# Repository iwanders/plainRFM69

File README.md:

plainRFM69
=========

This is a library for HopeRF's RFM69 radio series. The main goal of this library
is to use the hardware as efficiently as possible. With this goal in mind, the
used approach is different from that of the already existing libraries for this
radio module.

Approach
-------
The library is composed of two parts, the first; bareRFM69 provides a bare bones
interface to the hardware. It does nothing by itself and only provides methods
to interact with the hardware. Most of the configuration parameters are listed
in the header file. Constants are used for easy configuration and to prevent
having to look up parameters in the datasheet.
It uses the the new SPI transaction system.

The second part; plainRFM69, provides the user with more relevant functions for
sending messages. It allows for easy sending and receiving of packets. It
contains an internal buffer for received messages. Both receiving and
transmitting packets is done using the RFM69's AutoMode system. Which means the
radio spends as little time as possible in the transmitter phase and that
received packets can be retrieved from the module efficiently. This also allows
the send methods to be non-blocking, as it is unnecessary to wait until the
radio completes transmission.

Internal Workings
---------------
The plainRFM69 class provides several methods to configure the radio module with
its recommended parameters. The module is used in packet mode. Variable length
and address filtering is supported. 

The AutoMode system (described on page 42 of the RFM69CW datasheet) allows the
radio to change its mode based on a start condition, it then enters the
Intermediate Mode until an exit condition is met. 

### Receiving
By default, the radio is listening for packets. The AutoMode is configured such
that the radio goes to standby when a packet is received. This means that the
radio waits until that packet is retrieved by the microcontroller before it
starts listening for packets again. Retrieval of this packet is done with the
poll() method, which writes the packet to the internal buffer of plainRFM69.
Once the packet had been read, the radio automatically returns to listening to
packets.

### Sending
When a packet is to be transmitted, the radio is placed into standby mode. The
AutoMode is configured such that the radio automatically switches to transmitter
mode when there are bytes in the FIFO. It leaves transmission mode after the
packet is completely sent. This ensures that the transmitter is enabled 
exactly for the time necessary to sent the packet. The next time poll() is
called, the radio is configured for receiving packets with the AutoMode, as 
described in the previous paragraph.

### Interrupt
If the radio has received a packet, it waits in the Intermediate Mode until the
packet is read from the FIFO. When a packet is transmitted, the radio is in the
Intermediate Mode until the packet is completely sent. The radio module can
represent whether it is in the Intermediate State on a digital IO pin (DIO2).
In a slightly different way the same can be achieved using the DIO0 pin from the
radio module, see the `PingPongHPdio0` example on how to use that pin.

The microcontroller can attach an interrupt to this pin and call the poll()
method on every change. This means that if a packet is received, the
intermediate state is entered, DIO2 will switch from LOW to HIGH, resulting in
an interrupt trigger on the microcontroller, this calls poll() which reads the
packet from the FIFO, after this the radio automatically returns to receiving
state. The same method is possible with transmissions, where the poll() switches
the radio back to receiver mode after the transmission is complete. This means
that the microcontroller does not have to wait until the transmission is
complete, as this is also managed by the same interrupt and subsequent poll()
call. So the method to send a packet does not block until the transmission is
complete.

Testing & Performance
-------------------
The library was developed and tested on two [Teensy 3.1][teensy31]'s with
RFM69CW's attached. The pins used are described in the examples. The library is
tested with Arduino 1.0.6, 1.8.5. The DIO0 example was developed using
AdaFruit Feather M0 with the RFM69HCW radio module. Arduino and Moteino are also
known to work.

All tests were performed with the radio modules located next to each other. The
measured results are of course dependent on the parameters chosen, the
values from the examples show below use a GFSK modulation at 300000 bps.

#### Maximum_Speed
Sends 64 byte packets from the sender to the receiver. For every message sent
a counter is incremented. This counter is repeated in the message to create the
payload. At the receiver the payload is checked and the counter is used to check
whether there were missed packets.
```
Total packets: 101600
Packetloss count: 1
Per second: 416
```
This example can also be used to verify that the internal buffer is working. For
example when a delay is introduced in the loop of the receiver.

#### Maximum_PingPong
Sends 64 byte packets from the sender to the receiver, which echoes the packet,
the sender waits for this echo and checks the counter and message payload.
```
Successful pingpongs: 123468
Incorrect pingpongs: 0
Timeout pingpongs: 0
Successful / second: 188
Average ping (uSec): 5313
```

#### Buffering
The internal buffer of bareRFM69 is demonstrated in the BusyMan example. In this
example the interrupt mechanism is used and the receiving end is very busy in
the loop, this results in several messages queueing up in the internal buffer.
```
We are busy, doing important things!
Oh look, there are packets!
Packet (4): 2035
Packet (4): 2036
Packet (4): 2037
Packet (4): 2038
Packet (4): 2039
Packet (4): 2040
We had 6 packets in the buffer.
```

Usage
-----
As said, this library was created to be efficient. The goal was not really to be
user friendly. The examples were tested and are working without any known bugs.
Feel free to use it, but if it breaks you get to keep both parts, if you have a
fix for the problem feel free to share it.

The examples should provide pointers on how to use this, I suggest looking at
Minimal and MinimalInterrupt, where the latter should be the most minimal
implementation to build on. The internal buffering is shown in the BusyMan
example.

The header files for both bareRFM69 and plainRFM69 provide explanation of the
methods. If using a high power module, be sure to call `setHighPowerModule()` to
enable the high power functionality to be used.

Other libraries that might interest you are [Radiohead][radiohead] or
LowPowerLabs' [RFM69][rfm69] which have seen extensive testing.

The PCB's I designed to connect the radio modules to the Teensy can be found in
[extras/hardware/](extras/hardware/).

License
------
MIT License, see LICENSE.md.

Copyright (c) 2014 Ivor Wanders

[teensy31]: http://www.pjrc.com/teensy/
[radiohead]: http://www.airspayce.com/mikem/arduino/RadioHead/
[rfm69]: https://github.com/LowPowerLab/RFM69

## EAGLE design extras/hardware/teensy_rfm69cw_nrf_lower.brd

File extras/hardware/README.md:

Teensy_RFM69CW breakout
====================

This are the breakout boards I use to connect the radio module to the Teensy chips. I used two PCB's instead of one to save cost and to allow access to the pins below the radio module. Although only DIO2 is required for the library, all DIO pins are made accessible. The silkscreen on the boards is not all that clear, so I suggest opening the schematic and board files when soldering to check where the parts should go. I have switched to KiCad since making this, so I'm not going to invest any time in updating the boards.

The lower part has a jumper to connect the clock of the SPI port to either pin 13 or 14, it is connected to pin 14 by default so that the led is still available for use. This lower part also contains an 8 pin header for SPI, in the same pin-layout as the NRF24L0+ radio modules.

The upper part has a loading circuit for a LiPo battery, based on the [MAX1555][max1555] battery charger IC. It connects the Vusb from the Teensy to the USB input of the Max1555 chip, a header is provided for the DC pin of the Max1555 chip. The battery's positive lead is connected to the battery pin of the Max1555 IC and the Vin of the Teensy. Cutting the Vusb-Vin pad on the Teensy is required when using this board.

One wire is required from the upper to the lower board, this is the MISO line of the SPI port. I used a thick piece of wire for this in order to relieve the stress on the radio module when detaching the assembly from a Teensy. In case the board should also work without a battery attached, I recommend adding a larger electrolytic capacitor over the battery pins (something like 220uF should do).

Pinout for lower board
-------------

Related to the RFM69CW radio module:

| RFM           | Teensy |
| ------------- | ----------- |
| MOSI          |   11 DOUT |
| SCK           |   14 SCK2 (jumper to 13) |
| NSS           |   10 CS |
| DIO3          |   16 |

For the NRF header:

| NRF   |   Teensy |
| ------|--------- |
| CE    |   9 |
| SCK   |  14 SCK2 (jumper to 13) |
| MISO  |  12 DIN |
| CSN   |  15 CS |
| MOSI  |  11 DOUT |
| IRQ   |  Solderpad |

Pinout for the upper board
-------------------

Related to the RFM69CW radio module:

| RFM           | Teensy |
| ------------- | ----------- |
| MISO          |  Solderpad |
| RESET         |  23 |
| DIO0          |  2 |
| DIO1          |  1 |
| DIO2          |  0 |
| DIO5          | Solderpad |

Related to the charging Circuit:

| MAX1555       | Connected to          |
| ------------- | ----------- |
| Bat           | Battery header positive, Teensy Vin |
| DC            | DC input header positive |
| USB           | Teensy Vusb |
| CHG           | To an led |

Credits
---------
I used the Eagle part libraries from [Mikes-Eagle-Libraries](https://github.com/mgrusin/Mikes-Eagle-Libraries) and [SparkFun-PowerIC](https://github.com/sparkfun/SparkFun-Eagle-Libraries/blob/master/SparkFun-PowerIC.lbr). Inspiration to include the charging circuit came from [Onehorse's appallingly small LiPo Charger addon](https://forum.pjrc.com/threads/26462-Appallingly-small-LiPo-charger-add-on-for-Teensy-3-1).

Assembled
--------

[max1555]: https://www.maximintegrated.com/en/products/power/battery-management/MAX1555.html

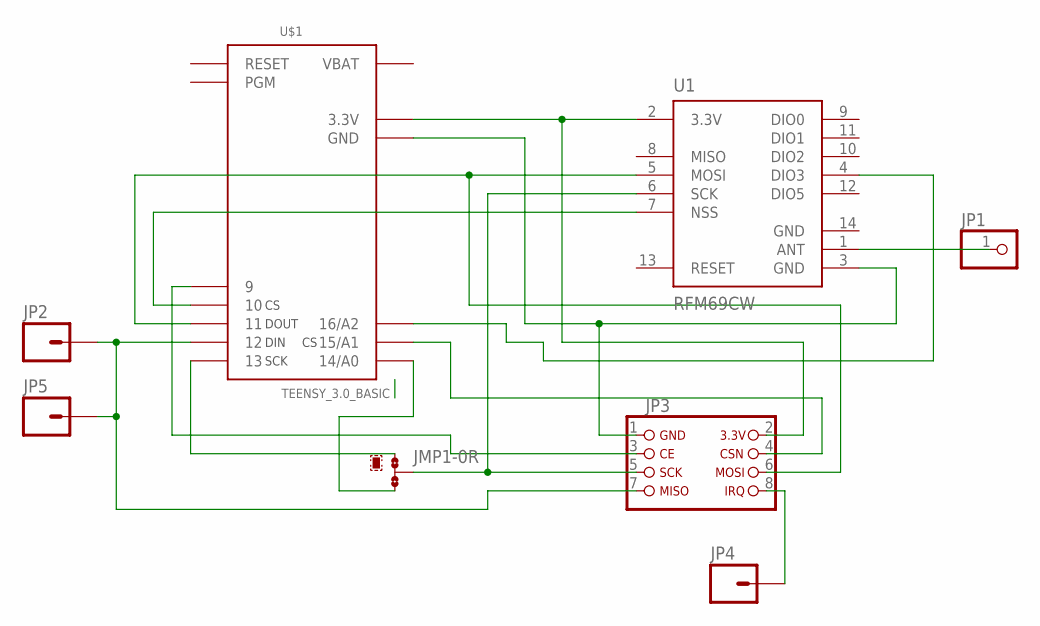
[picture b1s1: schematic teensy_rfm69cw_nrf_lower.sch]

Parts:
JMP1: 0R-JUMPA; A0R-JMP
JP1: PINHD-1X1; 1X01
JP2, JP4, JP5: M01SMD-4.5X1.5; PAD-1.5X4.5
JP3: NRF24
U1: RFM69CW; RFM69CW-XXXS2
U$1: TEENSY_3.0_BASIC

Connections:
GND: U1.14 (GND)
unnamed: JP3.2, U1.2 (3.3V), U$1.3.3V1 (3.3V)
unnamed: JP3.1, U1.3 (GND), U$1.GND1 (GND)
unnamed: JP3.4, U$1.15/A1
unnamed: JP3.6, U1.5 (MOSI), U$1.11
unnamed: JMP1.1, U$1.13
unnamed: JMP1.3, U$1.14/A0
unnamed: U1.7 (NSS), U$1.10
unnamed: U1.4 (DIO3), U$1.16/A2
unnamed: JP1.1, U1.1 (ANT)
unnamed: JMP1.2, JP3.5, U1.6 (SCK)
unnamed: JP2.P$1, JP3.7, JP5.P$1, U$1.12
unnamed: JP3.3, U$1.9
unnamed: JP3.8, JP4.P$1
VBAT: U$1.VBAT

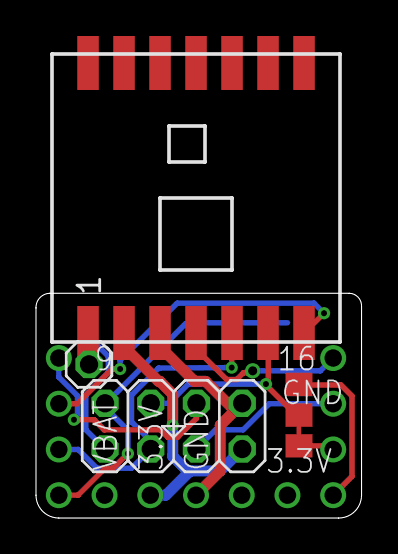
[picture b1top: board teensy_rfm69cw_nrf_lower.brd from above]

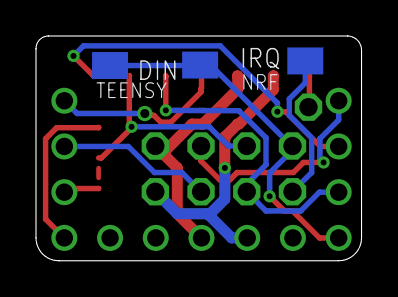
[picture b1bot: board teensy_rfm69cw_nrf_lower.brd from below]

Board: 2 copper layers, 18.1 x 12.5 mm, 8 parts (3 on the bottom side), 13 nets.

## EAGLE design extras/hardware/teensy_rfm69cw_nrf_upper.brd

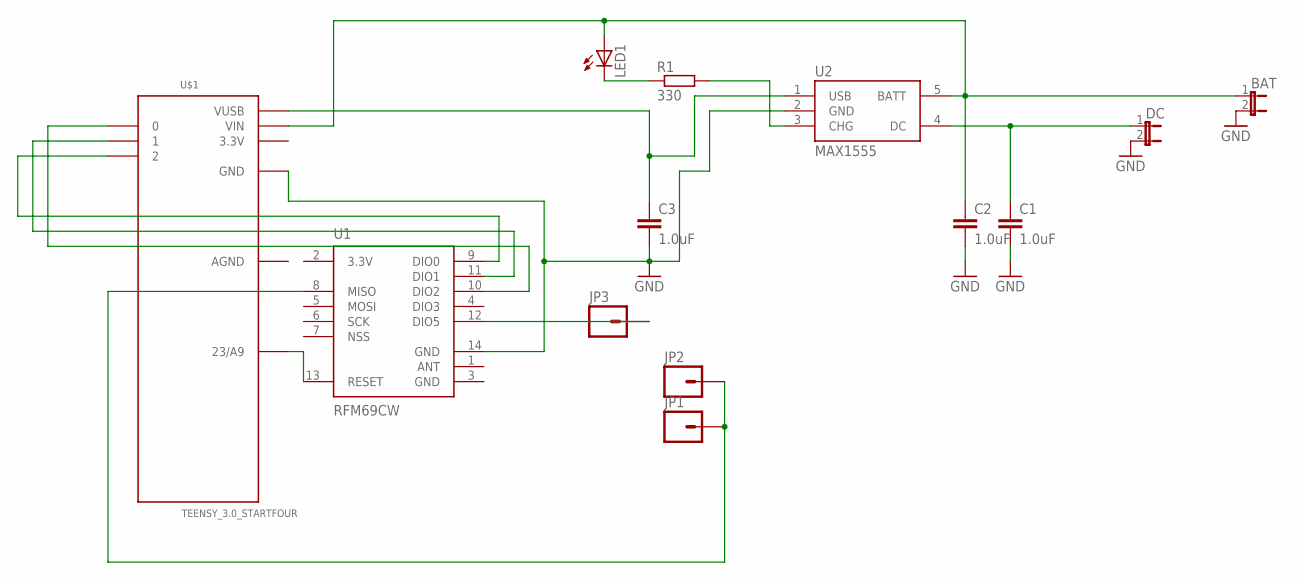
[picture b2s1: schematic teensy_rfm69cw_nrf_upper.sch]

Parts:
BAT: JP1E; JP1
C1, C2, C3: 1.0uF; 0603-CAP
DC: JP1E; JP1
JP1, JP2, JP3: M01SMD-4.5X1.5; PAD-1.5X4.5
LED1: LEDSML0603; SML0603
R1: 330; R0603
U1: RFM69CW; RFM69CW-XXXS2
U2: MAX1555; SOT23-5
U$1: TEENSY_3.0_STARTFOUR

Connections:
3.3V: U1.2 (3.3V), U$1.3.3V
AGND: U$1.AGND
GND: BAT.2, C1.2, C2.2, C3.2, DC.2, U1.3 (GND), U1.14 (GND), U2.2 (GND), U$1.GND
unnamed: LED1.C, R1.1
unnamed: U1.9 (DIO0), U$1.2
unnamed: U1.11 (DIO1), U$1.1
unnamed: U1.10 (DIO2), U$1.0
unnamed: U1.13 (RESET), U$1.23/A9
unnamed: C1.1, DC.1, U2.4 (DC)
unnamed: C3.1, U2.1 (USB), U$1.VUSB
unnamed: R1.2, U2.3 (CHG)
unnamed: JP1.P$1, JP2.P$1, U1.8 (MISO)
unnamed: BAT.1, C2.1, LED1.A, U2.5 (BATT), U$1.VIN
unnamed: JP3.P$1, U1.12 (DIO5)

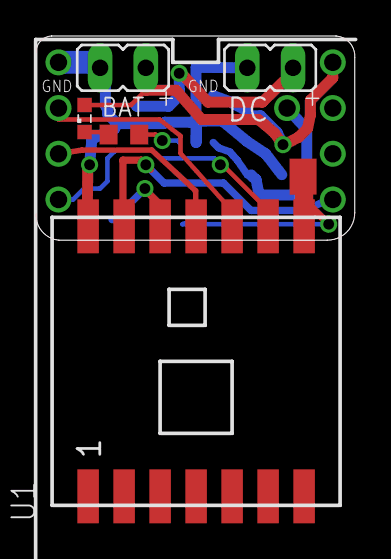
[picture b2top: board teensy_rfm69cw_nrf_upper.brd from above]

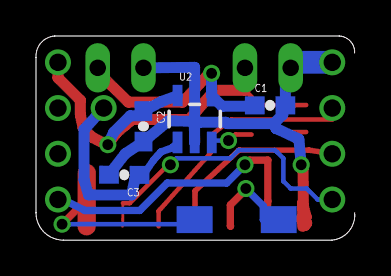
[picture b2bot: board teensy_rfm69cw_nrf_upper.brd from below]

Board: 2 copper layers, 17.7 x 11.3 mm, 13 parts (6 on the bottom side), 13 nets.

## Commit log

2014-12-07 Initial commit to Github.
    Makes the library publicly available.
2014-12-14 Fixes FIFO variable length limit.
    Correctly implements the maximum read length from FIFO.
2015-03-21 Fixes frequency calculation for non 32 bit platforms.
    With Arduino, setFrequency(400 * 1000 * 1000) was calculated as a 16 bit
    signed integer. This resulted in a wrongly set frequency. This fixes the
    calculation by ensuring a 32 unsigned integer is used.
2015-08-30 Improved support for Arduino UNO & Example.
    Changes headers from <WProgram.h> to <Arduino.h> for compatibility with
    the Arduino IDE, does not change anything for the Teensy.
    Adds an example which succesfully received packets when used with an
    Arduino UNO. Main problem was that the pin number is not identical
    to the interrupt number on this platform.
2015-10-22 Fixes name of calibration method for clarity.
    The previously named startRfCalibration method had nothing to do with
    the radio part of the module, it only pertained to the RC oscillator
    used for the Listen Modes. This rename reflects that and adds some
    explanation in the header file.
2015-10-22 Adds method to continuously emit a preamble.
    Disables the sequencer and turns on the transmitter, this results in
    a continuous transmission of the preamble.
2016-01-03 Adds breakout boards to extras folder.
    The Eagle files which I designed to connect the radio module to the
    Teensy has been added. Perhaps someone finds it useful.
2016-01-03 Fixes newlines in hardware description.
    Apparently newlines are required before the tables.
2016-03-01 Adds _very_ expirimental support for using DIO0 instead of DIO2.
    Uses the CRC ready and Packet sent interrupts instead of the automode interrupt.
    Still uses the automode system for efficiency in the radio module, only alerts
    the MCU to changes via another interrupt.
2016-06-27 Adds images of the schematics.
2016-09-18 Adds gitattribute to fix language statistics.
2018-05-27 setLNA() had incorrect type on LnaZin
    LnaZin was specified as bool. It needs to be 8 bit in order to have the correct bit field values for setting 200 ohm, which is recommended value in the datasheet and what is used in the example sketc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
2018-05-27 Changed second call to pinMode() to digitalWrite()
    Minor correction. The bareRFM69() constructor sets the cs_pin to output via pinMode() but accidentally calls pinMode() again when it looks like the intention was to initialize the chip select output 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
2018-06-01 Fix readme headings.
2018-08-20 Updated formatting, added support for high-power RFM69 modules and DIO0 interrupts.
2018-08-23 Added High Power module support, DIO0 example.
2018-08-23 Update changelog regarding hardware and dio0.
2020-01-11 Add passing modulation shaping to register.
2020-01-13 Correct DataMode flags.
2020-03-14 Change setFrequency signature to accomodate 868 MHz.

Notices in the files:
parts and their libraries:
SparkFun-Capacitors: Licensing: Creative Commons ShareAlike 4.0 International - https://creativecommons.org/licenses/by-sa/4.0
